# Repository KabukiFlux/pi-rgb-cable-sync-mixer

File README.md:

# RGBpi cable sync mixer

Small PCB mod to mix the sync in the RGBpi cable to solve sync issues

## Table of contents

- [Why](#why)
- [Description](#description)
- [Schematics](#schematics)
- [Install](#install)
- [Pics and final result](#pics-and-final-result)

## Why?

In order to eliminate/mitigate the sync issues on the cable we can do several options,
one is to use the common XOR mixer as usual, this other approach reduces the BOM
and enables the PCB to fit in the scart cable connector without any problem.

As you can see on this screenshot the original cable without modding induces a lot of 
DC bias on the sync causing some issues on some TVs, arcade monitors and so: 

With this mod we remove the DC offset not mixing into a full CSync signal but at least
we enable it to be used on more systems, of course the best approach is always the active sync
mixer with some gates but with this mod we restore at least the basic functionality.

Yes, the vertical period is not as good as with an active mixer but at least it removes the sync
issues on most devices with a very small BOM.

### OSSC comparison

Without modding:

Modded cable:

## Description

This is intended to be a very small PCB to be included inside the scart connector on the rgbpi cable.

It is valid for all the rgbpi cable versions, we will see on the installation procedure V1 and V2 cables.

In the BOM directory there's an interactive BOM with all the required components.

In the gerbers directory we have the gerbers to manufacture the boards.

In the KiCAD folder we can find the KiCAD project itself.

## Schematics

You can find here as well as the KiCAD files inside the KiCAD folder.

## Install

1- Send to manufacture the GERBER board to JLCPCB or other PCB manufacturer.

2- Get the components required, you can see here the Bill Of Materials [BOM](bom/ibom.html)

3- Solder the components.

4- Follow the procedure depending on your cable version.

### Detect your cable version

This is what we will call V1, follow the V1 install procedure:

This is what we will call V2, follow the V2 install procedure:

### V1 cable install

If your cable is V1 then:

* Check the wires for the installation

* Check the soldering positions

* Solder as shown (the big white cable is not required by this mod)

### V2 cable install

If your cable is V2 then:

* Check the wires for the installation

* Check the soldering positions

* Place as shown

* Solder the scart part (you can use for GND the 3rd pin from the bottom, it is better)

* Solder the cable hsync and vsync wires

### Pics and final result

V1:

V2

That's it.

I'm not responsible
============
And yes, read below, no responsibility taken on bad use.

Special thanks to Retroark [here on X](https://twitter.com/retroark) 

DISCLAIMER (See Licensing)
==========================
See LICENSE fo more information.

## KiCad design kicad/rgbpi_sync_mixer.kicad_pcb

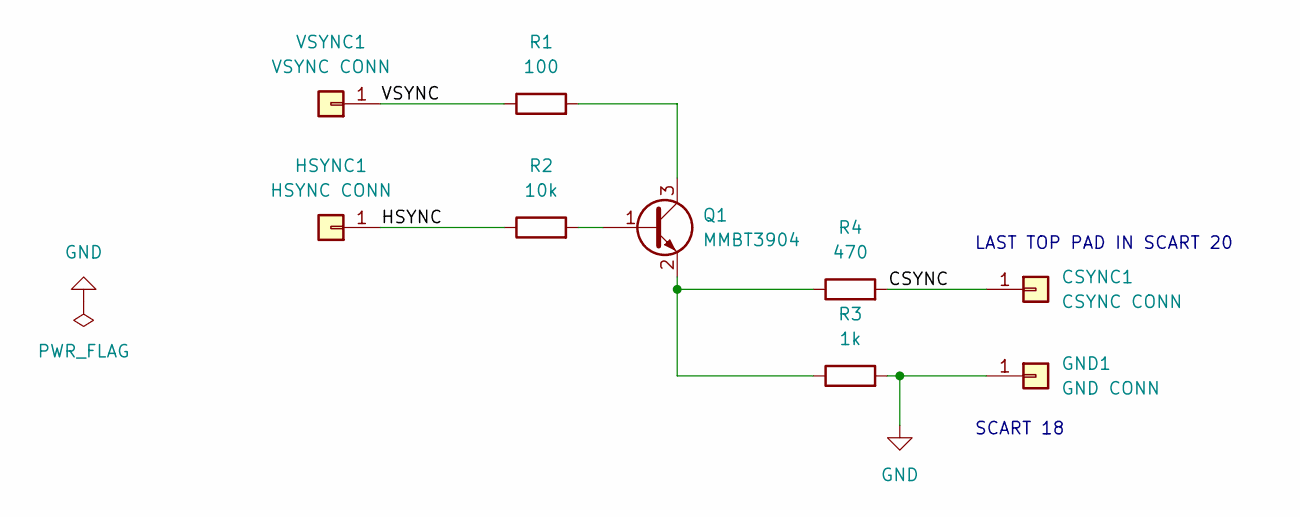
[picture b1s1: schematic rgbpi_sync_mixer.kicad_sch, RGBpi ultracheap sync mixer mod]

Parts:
CSYNC1: CSYNC CONN; SolderWirePad_1x01_SMD_1x2mm
GND1: GND CONN; SolderWirePad_1x01_SMD_1x2mm
HSYNC1: HSYNC CONN; SolderWirePad_1x01_SMD_1x2mm
Q1: MMBT3904; SOT-23
R1: 100; R_0402_1005Metric
R2: 10k; R_0402_1005Metric
R3: 1k; R_0402_1005Metric
R4: 470; R_0402_1005Metric
VSYNC1: VSYNC CONN; SolderWirePad_1x01_SMD_1x2mm

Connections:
/CSYNC: CSYNC1.1, R4.2
/HSYNC: HSYNC1.1, R2.1
/VSYNC: R1.1, VSYNC1.1
GND: GND1.1, R3.2
unnamed: Q1.1 (B), R2.2
unnamed: Q1.3 (C), R1.2
unnamed: Q1.2 (E), R3.1, R4.1

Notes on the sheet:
LAST TOP PAD IN SCART 20
SCART 18

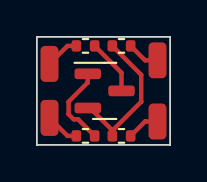
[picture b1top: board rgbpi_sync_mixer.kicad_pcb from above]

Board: 2 copper layers, 7.4 x 6.0 mm, 9 parts (0 on the bottom side), 7 nets.

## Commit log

2024-01-25 RGBpi ultracheap sync mixer mod upload
